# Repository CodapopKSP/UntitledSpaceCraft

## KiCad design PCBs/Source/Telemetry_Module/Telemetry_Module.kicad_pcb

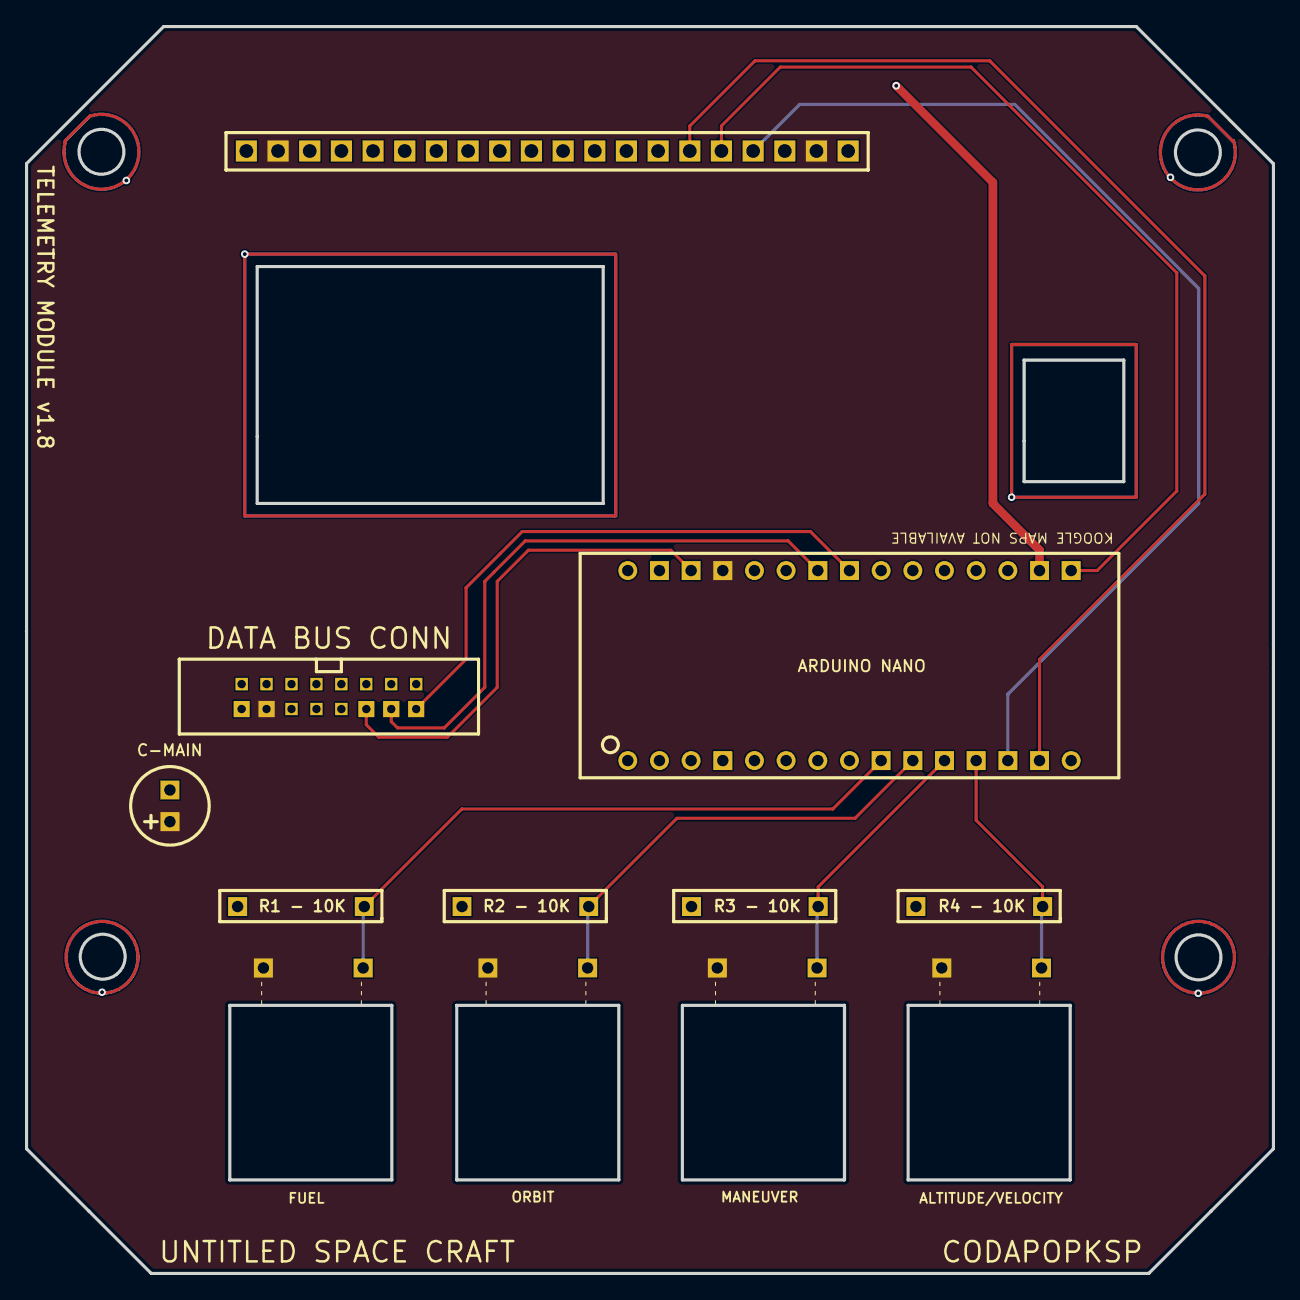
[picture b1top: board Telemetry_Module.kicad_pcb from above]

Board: 2 copper layers, 100.0 x 100.0 mm, 51 parts (0 on the bottom side), 12 nets.

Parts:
ARDUINO NANO: Arduino_Nano_Header; DIP-30_L43.18-W15.24-ARDUINONANO
C-MAIN: 10uf; CAP-D6.3×F2.5
NONE1: _
R1, R2, R3, R4: - 10K; TH_RES_10mm
TP_+5V, TP_+5V#2, TP_+5V#3, TP_+5V#4, TP_+5V#5, TP_+5V#6: WirePad
TP_E: WirePad
TP_GND: WirePad
TP_GND#2, TP_GND#3: WirePad
TP_Pad_gge18733, TP_Pad_gge18817, TP_Pad_gge18832, TP_Pad_gge18847, TP_Pad_gge18877, TP_Pad_gge18892, TP_Pad_gge18907, TP_Pad_gge18922, TP_Pad_gge18937, TP_Pad_gge18952, TP_Pad_gge18967, TP_Pad_gge18982: WirePad
TP_RS: WirePad
TP_R_W: WirePad
TP_T1, TP_T2, TP_T3, TP_T4: WirePad
WP1, WP2, WP3, WP4, WP5, WP6, WP7, WP8, WP9, WP10, WP11, WP12, WP13, WP14, WP15, WP16: WPAD-1-30AWG; WPAD-1-PTH-30AWG

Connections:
+5V: ARDUINO NANO.27, C-MAIN.1, TP_+5V.20, TP_+5V#4.17, WP7.1
E: ARDUINO NANO.14, TP_E.30
GND: ARDUINO NANO.4, ARDUINO NANO.29, C-MAIN.2, R1.2, R2.2, R3.2, R4.2, TP_GND.21, TP_GND#2.16, TP_GND#3.21, WP8.1
R/W: ARDUINO NANO.16, TP_R_W.17
RESET: ARDUINO NANO.28, WP3.1
RS: ARDUINO NANO.13, TP_RS.18
SCL: ARDUINO NANO.24, WP2.1
SDA: ARDUINO NANO.23, WP1.1
T1: ARDUINO NANO.9, R1.1
T2: ARDUINO NANO.10, R2.1
T3: ARDUINO NANO.11, R3.1
T4: ARDUINO NANO.12, R4.1

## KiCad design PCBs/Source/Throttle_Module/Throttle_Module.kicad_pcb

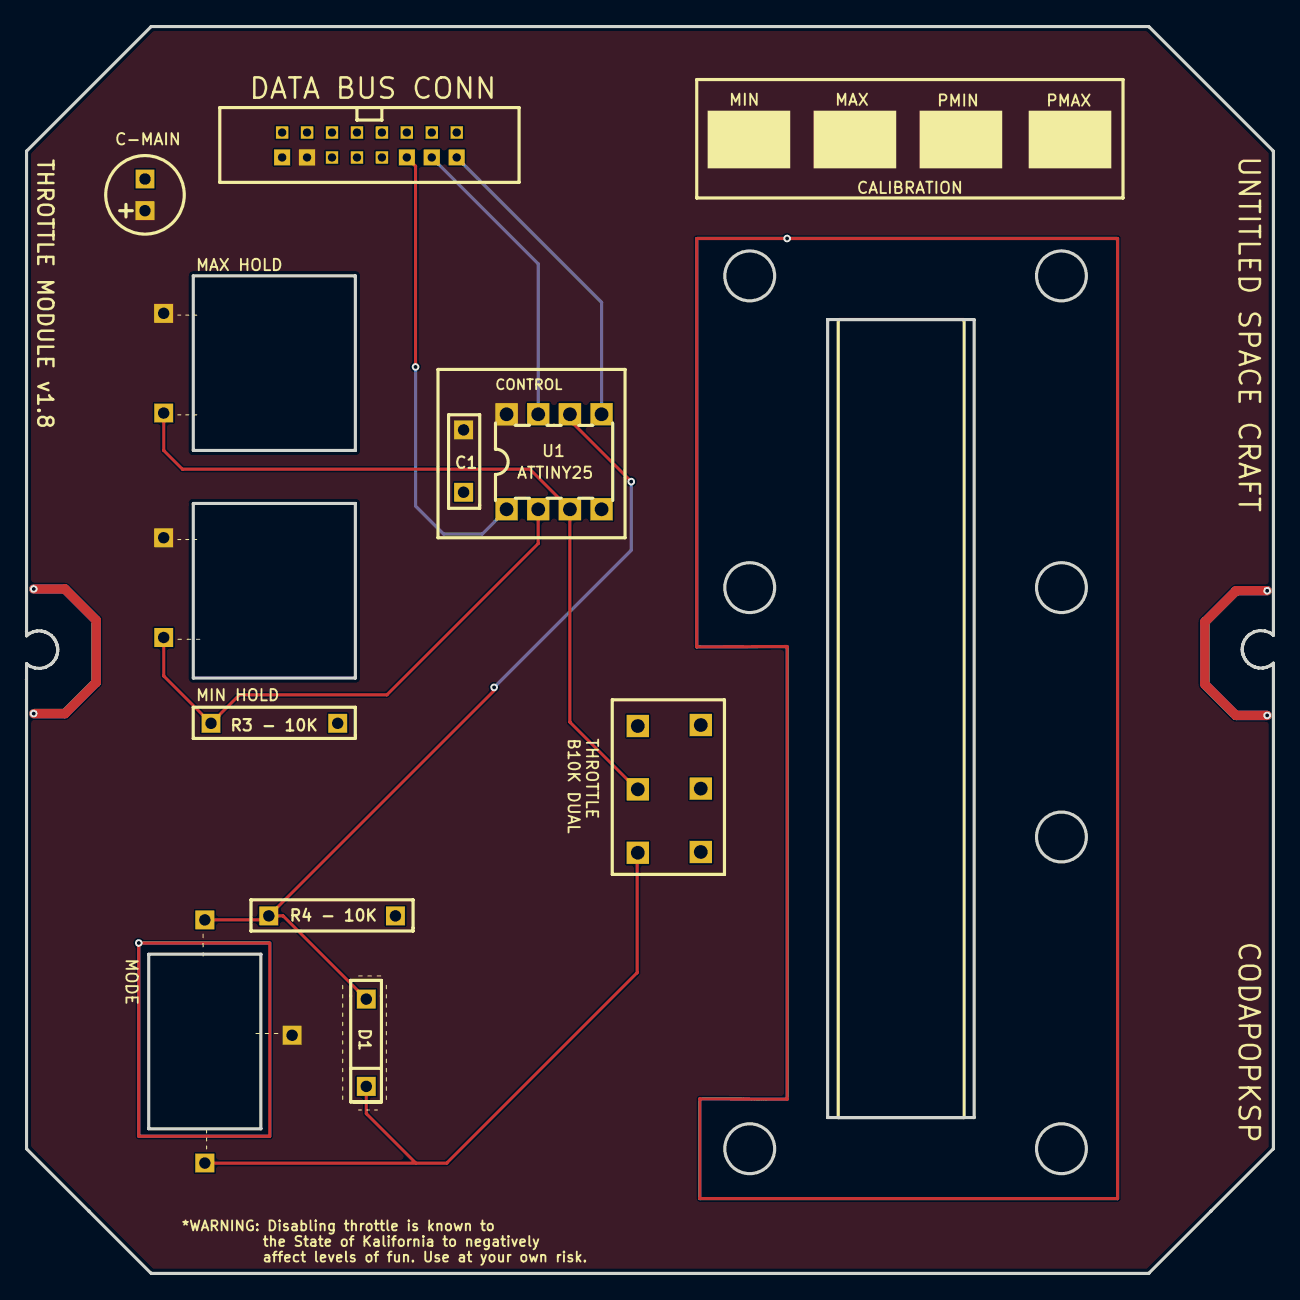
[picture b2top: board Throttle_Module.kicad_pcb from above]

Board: 2 copper layers, 100.0 x 100.0 mm, 36 parts (0 on the bottom side), 9 nets.

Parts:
C1: C104; TH_CAP_5mm
C-MAIN: 10uf; CAP-D6.3×F2.5
R3, R4: - 10K; TH_RES_10mm
TP_+5V, TP_+5V#2, TP_+5V#3: WirePad
TP_GND: WirePad
TP_MINHOLD: WirePad
TP_PCONT: WirePad
TP_PCONT#2: WirePad
TP_POWER: WirePad
TP_POWER#2, TP_POWER#3: WirePad
TP_Pad_gge22046, TP_Pad_gge22136, TP_Pad_gge22247: WirePad
TP_THROTTLE: WirePad
TP_THROTTLE#2: WirePad
U1: ATtiny25; PDIP-8_L9.3-W6.4-P2.54-LS7.6-BL
WP54, WP55, WP56, WP57, WP58, WP59, WP60, WP61, WP62, WP63, WP64, WP65, WP66, WP67, WP68, WP69: WPAD-1-30AWG; WPAD-1-PTH-30AWG

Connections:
+5V: C1.2, C-MAIN.1, TP_+5V.1, TP_+5V#2.1, TP_+5V#3.1, U1.8, WP61.1
GND: C1.1, C-MAIN.2, R3.1, R4.1, TP_GND.3, U1.4, WP62.1
MINHOLD: R3.2, TP_MINHOLD.1, U1.2
PCONT: R4.2, TP_PCONT.5, TP_PCONT#2.1, U1.6
POWER: TP_POWER.1, TP_POWER#2.4, TP_POWER#3.4
RESET: U1.1, WP57.1
SCL: U1.7, WP56.1
SDA: U1.5, WP55.1
THROTTLE: TP_THROTTLE.2, TP_THROTTLE#2.1, U1.3

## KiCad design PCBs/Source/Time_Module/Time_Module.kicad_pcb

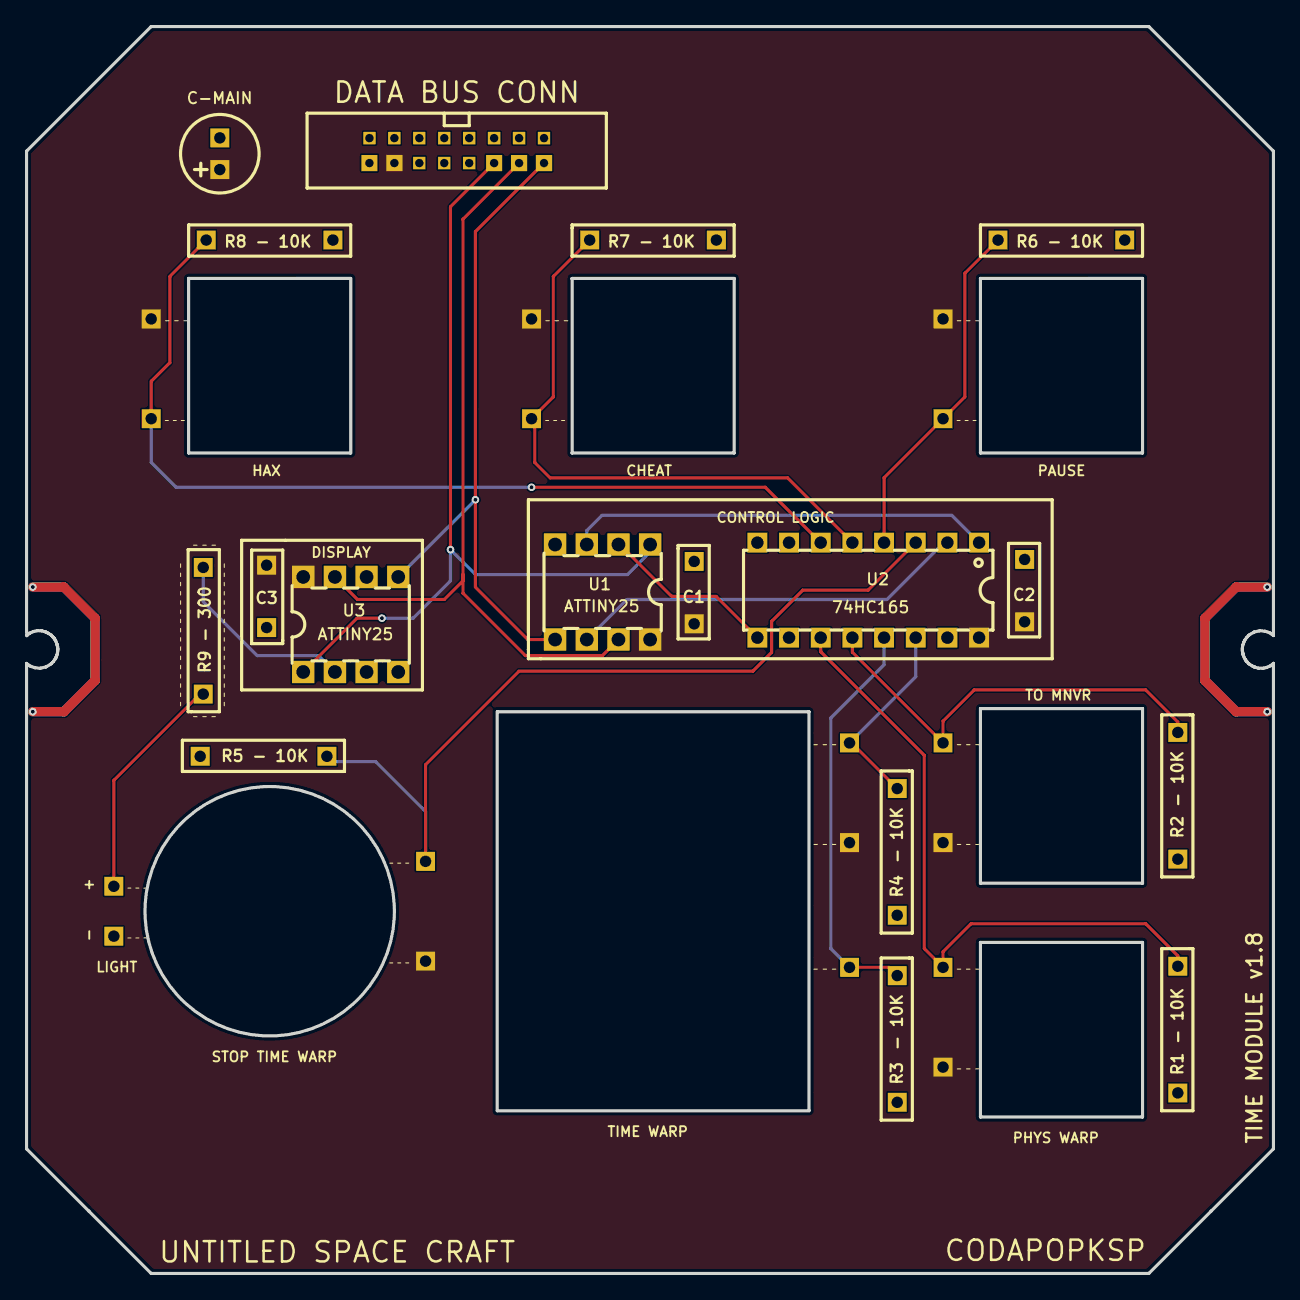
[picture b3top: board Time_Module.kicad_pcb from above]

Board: 2 copper layers, 100.0 x 100.0 mm, 51 parts (0 on the bottom side), 17 nets.

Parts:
C1, C2, C3: C104; TH_CAP_5mm
C-MAIN: 10uf; CAP-D6.3×F2.5
NONE: _
R1, R2, R3, R4, R5, R6, R7, R8: - 10K; TH_RES_10mm
R9: - 300; TH_RES_10mm
TP_+5V, TP_+5V#2, TP_+5V#3, TP_+5V#4, TP_+5V#5, TP_+5V#6, TP_+5V#7: WirePad
TP_GND: WirePad
TP_T1, TP_T2, TP_T3, TP_T4, TP_T5, TP_T6, TP_T7, TP_T8: WirePad
TP_TLIGHT: WirePad
U1, U3: ATtiny25; PDIP-8_L9.3-W6.4-P2.54-LS7.6-BL
U2: 74HC165; DIP-16_L20.0-W6.4-P2.54-LS7.6-BL
WIRE1: _
WP1, WP2, WP3, WP4, WP5, WP6, WP7, WP8, WP9, WP10, WP11, WP12, WP13, WP14, WP15, WP16: WPAD-1-30AWG; WPAD-1-PTH-30AWG

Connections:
+5V: C1.2, C2.2, C3.2, C-MAIN.1, U1.8, U2.16, U3.8, WP7.1
CLOCK(Y): U1.6, U2.2
DATA(P): U1.2, U2.9
GND: C1.1, C2.1, C3.1, C-MAIN.2, R1.2, R2.2, R3.2, R4.2, R5.2, R6.2, R7.2, R8.2, U1.4, U2.8, U2.15, U3.4, WP8.1
LATCH(G): U1.3, U2.1
LIGHT1: R9.2, U3.2
RESET: U1.1, U3.1, WP3.1
SCL: U1.7, U3.7, WP2.1
SDA: U1.5, U3.5, WP1.1
T1: R1.1, U2.11
T2: R2.1, U2.12
T3: R3.1, U2.13
T4: R4.1, U2.14
T5: R5.1, U2.3
T6: R6.1, U2.4
T7: R7.1, U2.5
T8: R8.1, U2.6

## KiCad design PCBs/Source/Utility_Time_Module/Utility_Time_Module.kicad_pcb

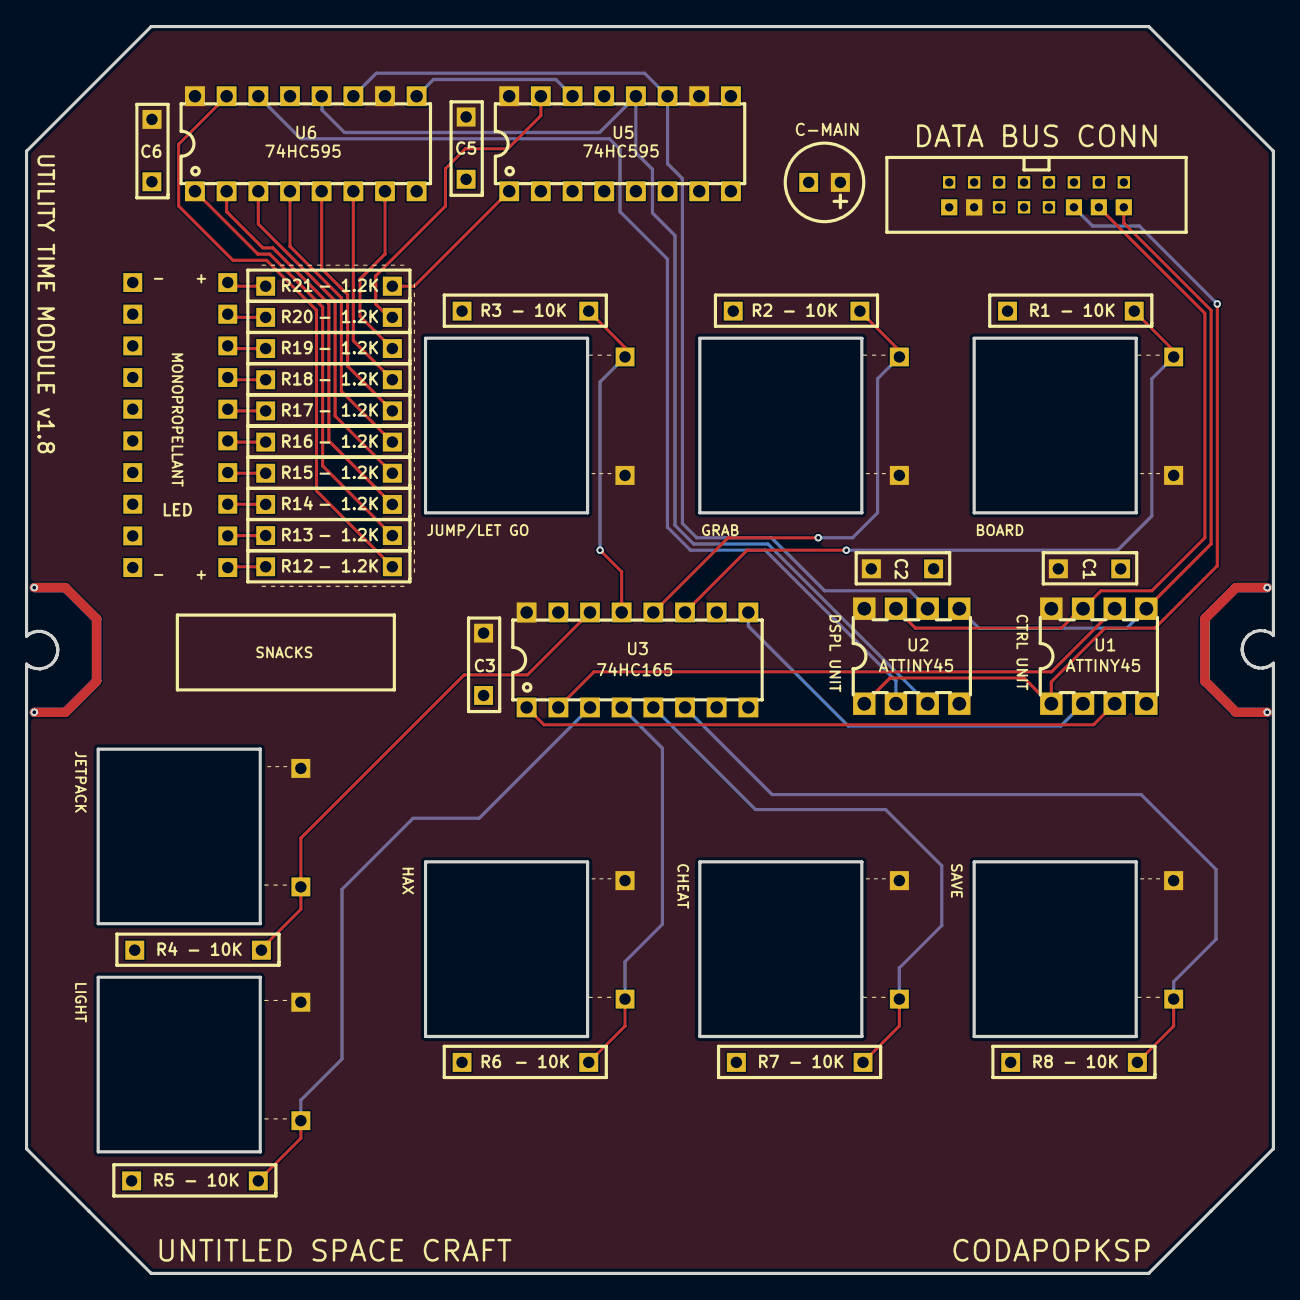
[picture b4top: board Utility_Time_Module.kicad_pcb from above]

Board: 2 copper layers, 100.0 x 100.0 mm, 62 parts (0 on the bottom side), 40 nets.

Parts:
C1, C2, C3, C5, C6: C104; TH_CAP_5mm
C-MAIN: 10uf; CAP-D6.3×F2.5
LED: _
R1, R2, R3, R4, R5, R6, R7, R8: - 10K; TH_RES_10mm
R12, R13, R14, R15, R16, R17, R18, R19, R20, R21: - 1.2K; TH_RES_10mm
TP_+5V, TP_+5V#2, TP_+5V#3, TP_+5V#4, TP_+5V#5, TP_+5V#6, TP_+5V#7, TP_+5V#8: WirePad
TP_EVA1, TP_EVA2, TP_EVA3, TP_EVA4, TP_EVA5: WirePad
TP_T1, TP_T2, TP_T3: WirePad
U1, U2: ATtiny45; PDIP-8_L9.3-W6.4-P2.54-LS7.6-BL
U3: 74HC165; DIP-16_L20.0-W6.4-P2.54-LS7.6-BL
U5, U6: 74HC595; DIP-16_L20.0-W6.4-P2.54-LS7.6-BL
WP1, WP2, WP3, WP4, WP5, WP6, WP7, WP8, WP9, WP10, WP11, WP12, WP13, WP14, WP15, WP16: WPAD-1-30AWG; WPAD-1-PTH-30AWG

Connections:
+5V: C1.2, C2.2, C3.2, C5.2, C6.2, C-MAIN.1, TP_+5V.9, TP_+5V#2.8, TP_+5V#3.11, TP_+5V#5.15, TP_+5V#8.8, U1.8, U2.8, U3.16, U5.10, U5.16, U6.10, U6.16, WP7.1
CLOCK(Y): U1.6, U3.2
CLOCK(Y)2: U2.6, U5.11, U6.11
DATA(B)2: U5.14, U6.9
DATA(P): U1.2, U3.9
DATA(P)2: U2.2, U6.14
EVA1: R1.1, TP_EVA1.20, U3.11
EVA2: R2.1, TP_EVA2.18, U3.12
EVA3: R3.1, TP_EVA3.16, U3.13
EVA4: R4.1, TP_EVA4.1, U3.14
EVA5: R5.1, TP_EVA5.1, U3.3
GND: C1.1, C2.1, C3.1, C5.1, C6.1, C-MAIN.2, LED.GND, R1.2, R2.2, R3.2, R4.2, R5.2, R6.2, R7.2, R8.2, U1.4, U2.4, U3.8, U3.15, U5.8, U5.13, U6.8, U6.13, WP8.1
LATCH(G): U1.3, U3.1
LATCH(G)2: U2.3, U5.12, U6.12
LIGHT1: R12.1, U6.15
LIGHT2: R13.1, U6.1
LIGHT3: R14.1, U6.2
LIGHT4: R15.1, U6.3
LIGHT5: R16.1, U6.4
LIGHT6: R17.1, U6.5
LIGHT7: R18.1, U6.6
LIGHT8: R19.1, U6.7
LIGHT9: R20.1, U5.15
LIGHT10: R21.1, U5.1
RESET: U1.1, U2.1, WP3.1
SCL: U1.7, U2.7, WP2.1
SDA: U1.5, U2.5, WP1.1
T1: R6.1, TP_T1.2, U3.4
T2: R7.1, U3.5
T3: R8.1, TP_T3.4, U3.6
WP41_1: LED.GND, R19.2
WP42_1: LED.GND, R18.2
WP43_1: LED.GND, R17.2
WP44_1: LED.GND, R16.2
WP45_1: LED.GND, R15.2
WP46_1: LED.GND, R14.2
WP47_1: LED.GND, R13.2
WP48_1: LED.GND, R12.2
WP58_1: LED.GND, R20.2
WP60_1: LED.GND, R21.2
